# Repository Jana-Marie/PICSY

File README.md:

# PICSY

**UNDER DEVELOPMENT...**

An ESP32 based Pixel-Art-Camera, shooting color-indexed pixel art alike PNGs directly onto an SD card.

<table>
  <tbody>
    <tr>
      <td colspan="2">
        
      </td>
    </tr>
    <tr>
      <td>
        
      </td>
      <td>
        
      </td>
    </tr>
    <tr>
      <td colspan="2">
        
      </td>
    </tr>
    <tr>
      <td colspan="2">
        
      </td>
    </tr>
    <tr>
      <td>
        
      </td>
      <td>
        
      </td>
    </tr>
    <tr>
      <td colspan="2">
        
      </td>
    </tr>
  </tbody>
</table>

### Setup

Flash micropython as per [/main/micropython-bin](https://github.com/Jana-Marie/PICSY/tree/main/micropython-bin), afterwards copy `ubuf2png.py` onto the ESP32-CAM with `ampy -p /dev/ttyUSB0 -b 115200 put ubuf2png.py`

### Usage

This is WIP and will be moved to saving the PNG to a SD card directly soon.

#### Manual usage

Place an SD card into the SD-Card slot and run

```
ampy -p /dev/ttyUSB0 -b 115200 run boot.py
```

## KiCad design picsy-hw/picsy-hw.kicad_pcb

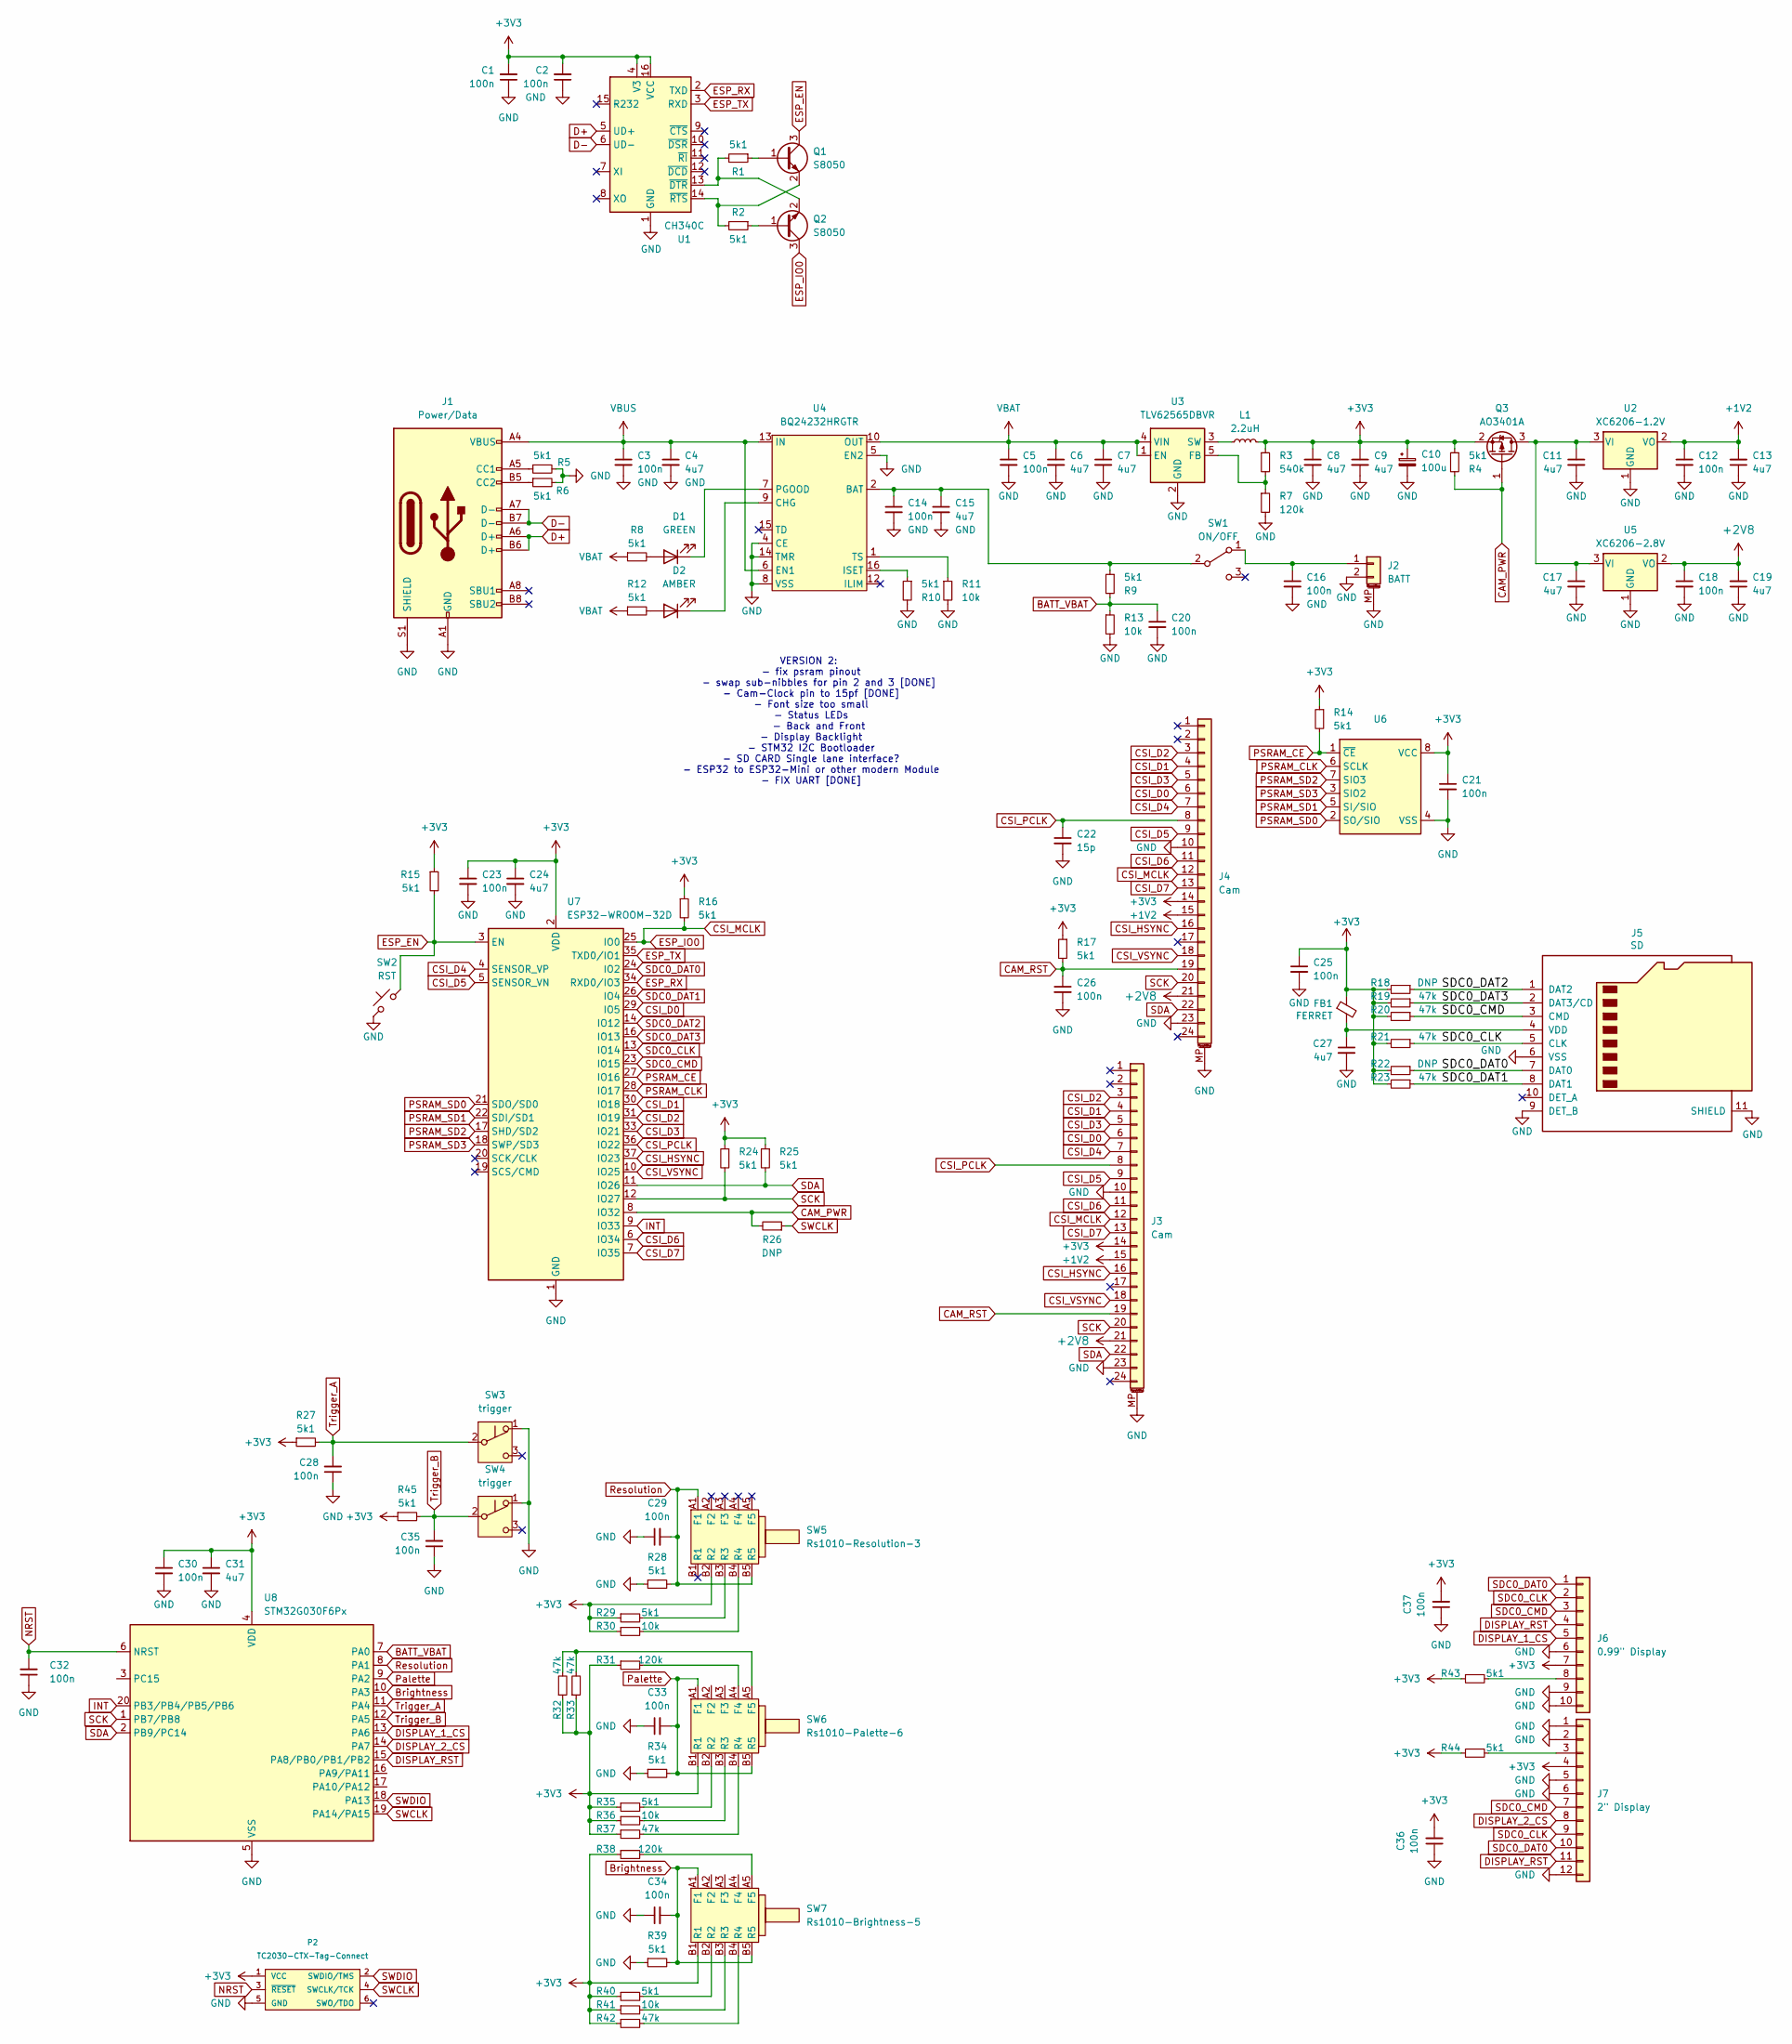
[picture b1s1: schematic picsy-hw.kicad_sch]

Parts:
C1, C2, C3, C5, C12, C14, C16, C18, C20, C21, C23, C25, C26, C28, C29, C30, C32, C33, C34, C35, C36, C37: 100n; C_0402
C4, C6, C7, C8, C9, C11, C13, C15, C17, C19, C24, C27, C31: 4u7; C_0603
C10: 100u; CP_Elec_6.3x5.4
C22: 15p; C_0402
D1: GREEN; LED_0603_1608Metric
D2: AMBER; LED_0603_1608Metric
FB1: FERRET; R_0805
J1: Power/Data; USB-C 16Pin
J2: BATT; Molex_PicoBlade_53261-0271_1x02-1MP_P1.25mm_Horizontal
J3, J4: Cam; TE_2-1734839-4_1x24-1MP_P0.5mm_Horizontal
J5: SD; microSD_HC_Hirose_DM3D-SF
J6: 0.99" Display; 0.99Inch-IPS-GC9D01
J7: 2" Display; 2.0Inch-IPS-ST7789
L1: 2.2uH; L_2512_6332Metric
P2: TC2030-CTX-Tag-Connect; TC2030
Q1, Q2: S8050; SOT-23
Q3: AO3401A; SOT-23
R1, R2, R4, R5, R6, R8, R9, R10, R12, R14, R15, R16, R17, R24, R25, R27, R28, R29, R34, R35, R39, R40, R43, R44, R45: 5k1; R_0402
R3: 540k; R_0402
R7, R31, R38: 120k; R_0402
R11, R13, R30, R36, R41: 10k; R_0402
R18, R22, R26: DNP; R_0402
R19, R20, R21, R23, R32, R33, R37, R42: 47k; R_0402
SW1: ON/OFF; SK-12D07VG4
SW2: RST; SW_SPST_EVQP7C
SW3: trigger; Microswitch_L
SW4: trigger; Microswitch_R
SW5: Rs1010-Resolution-3; Rs1010
SW6: Rs1010-Palette-6; Rs1010
SW7: Rs1010-Brightness-5; Rs1010
U1: CH340C; SOIC-16_3.9x9.9mm_P1.27mm
U2: XC6206-1.2V; SOT-23-3
U3: TLV62565DBVR; SOT-23-5
U4: BQ24232HRGTR; QFN-16-1EP_3x3mm_P0.5mm_EP1.7x1.7mm
U5: XC6206-2.8V; SOT-23-3
U6: SOIC-8_3.9x4.9mm_P1.27mm
U7: ESP32-WROOM-32D; ESP32-WROOM-32U
U8: STM32G030F6Px; TSSOP-20_4.4x6.5mm_P0.65mm

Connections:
+1V2: C12.1, C13.2, J3.15, J4.15, U2.2 (VO)
+2V8: C18.1, C19.2, J3.21, J4.21, U5.2 (VO)
+3V3: C1.2, C2.2, C8.1, C9.1, C10.1, C21.1, C23.1, C24.1, C25.1, C30.1, C31.1, C36.2, C37.2, FB1.1, J3.14, J4.14, J6.7, J7.4, L1.2, P2.1 (VCC), Q3.2 (S), R3.1, R4.1, R14.1, R15.1, R16.1, R17.1, R18.2, R19.2, R20.2, R21.2, R22.2, R23.2, R24.1, R25.1, R27.1, R29.1, R30.1, R31.1, R32.1, R33.1, R35.1, R36.1, R37.1, R38.1, R40.1, R41.1, R42.1, R43.1, R44.1, R45.1, SW5.B2 (R2), SW6.B1 (R1), SW7.B1 (R1), U1.4 (V3), U1.16 (VCC), U6.8 (VCC), U7.2 (VDD), U8.4 (VDD)
BATT_VBAT: C20.1, R9.2, R13.1, U8.7 (PA0)
Brightness: C34.2, R39.2, SW7.A1 (F1), SW7.B5 (R5), U8.10 (PA3)
CAM_PWR: Q3.1 (G), R4.2, R26.2, U7.8 (IO32)
CAM_RST: C26.1, J3.19, J4.19, R17.2
CSI_D0: J3.6, J4.6, U7.29 (IO5)
CSI_D1: J3.4, J4.4, U7.30 (IO18)
CSI_D2: J3.3, J4.3, U7.31 (IO19)
CSI_D3: J3.5, J4.5, U7.33 (IO21)
CSI_D4: J3.7, J4.7, U7.4 (SENSOR_VP)
CSI_D5: J3.9, J4.9, U7.5 (SENSOR_VN)
CSI_D6: J3.11, J4.11, U7.6 (IO34)
CSI_D7: J3.13, J4.13, U7.7 (IO35)
CSI_HSYNC: J3.16, J4.16, U7.37 (IO23)
CSI_MCLK: J3.12, J4.12, Q2.3 (C), R16.2, U7.25 (IO0)
CSI_PCLK: C22.1, J3.8, J4.8, U7.36 (IO22)
CSI_VSYNC: J3.18, J4.18, U7.10 (IO25)
D+: J1.A6 (D+), J1.B6 (D+), U1.5 (UD+)
D-: J1.A7 (D-), J1.B7 (D-), U1.6 (UD-)
DISPLAY_1_CS: J6.5, U8.13 (PA6)
DISPLAY_2_CS: J7.8, U8.14 (PA7)
DISPLAY_RST: J6.4, J7.11, U8.15 (PA8/PB0/PB1/PB2)
ESP_EN: Q1.3 (C), R15.2, SW2.1, U7.3 (EN)
GND: C1.1, C2.1, C3.2, C4.2, C5.2, C6.2, C7.2, C8.2, C9.2, C10.2, C11.2, C12.2, C13.1, C14.2, C15.2, C16.2, C17.2, C18.2, C19.1, C20.2, C21.2, C22.2, C23.2, C24.2, C25.2, C26.2, C27.2, C28.1, C29.1, C30.2, C31.2, C32.1, C33.1, C34.1, C35.1, C36.1, C37.1, J1.A1 (GND), J1.A12 (GND), J1.B1 (GND), J1.B12 (GND), J1.S1 (SHIELD), J2.2, J2.MP (MountPin), J3.10, J3.23, J3.MP (MountPin), J4.10, J4.23, J4.MP (MountPin), J5.6 (VSS), J5.9 (DET_B), J5.11 (SHIELD), J6.6, J6.9, J6.10, J7.1, J7.2, J7.5, J7.6, J7.12, P2.5 (GND), R5.2, R6.2, R7.2, R10.2, R11.2, R13.2, R28.1, R34.1, R39.1, SW2.2, SW3.1 (A), SW4.1 (A), U1.1 (GND), U2.1 (GND), U3.2 (GND), U4.4 (CE), U4.5 (EN2), U4.8 (VSS), U4.14 (TMR), U4.17 (VSS), U5.1 (GND), U6.4 (VSS), U7.1 (GND), U7.15 (GND), U7.38 (GND), U7.39 (GND), U8.5 (VSS)
INT: U7.9 (IO33), U8.20 (PB3/PB4/PB5/PB6)
NRST: C32.2, P2.3 (~RESET), U8.6 (NRST)
unnamed: D1.2 (A), R8.2
unnamed: D1.1 (K), U4.7 (PGOOD)
unnamed: D2.2 (A), R12.2
unnamed: D2.1 (K), U4.9 (CHG)
unnamed: J1.A5 (CC1), R5.1
unnamed: J1.B5 (CC2), R6.1
unnamed: C16.1, J2.1, SW1.1 (A)
unnamed: C27.1, FB1.2, J5.4 (VDD)
unnamed: J6.8, R43.2
unnamed: J7.3, R44.2
unnamed: Q1.1 (B), R1.1
unnamed: Q1.2 (E), R2.2, U1.14 (~RTS)
unnamed: Q2.1 (B), R2.1
unnamed: Q2.2 (E), R1.2, U1.13 (~DTR)
unnamed: C11.1, C17.1, Q3.3 (D), U2.3 (VI), U5.3 (VI)
unnamed: C14.1, C15.1, R9.1, SW1.2 (B), U4.2 (BAT), U4.3 (BAT)
unnamed: R29.2, SW5.B3 (R3)
unnamed: R30.2, SW5.B4 (R4)
unnamed: R31.2, SW6.A4 (F4)
unnamed: R32.2, R33.2, SW6.A5 (F5)
unnamed: R35.2, SW6.B2 (R2)
unnamed: R36.2, SW6.B3 (R3)
unnamed: R37.2, SW6.B4 (R4)
unnamed: R38.2, SW7.A5 (F5)
unnamed: R40.2, SW7.B2 (R2)
unnamed: R41.2, SW7.B3 (R3)
unnamed: R42.2, SW7.B4 (R4)
unnamed: R3.2, R7.1, U3.5 (FB)
unnamed: L1.1, U3.3 (SW)
unnamed: R10.1, U4.16 (ISET)
unnamed: R11.1, U4.1 (TS)
PSRAM_CE: R14.2, U6.1 (~CE), U7.27 (IO16)
PSRAM_CLK: U6.6 (SCLK), U7.28 (IO17)
PSRAM_SD0: U6.2 (SO/SIO), U7.21 (SDO/SD0)
PSRAM_SD1: U6.5 (SI/SIO), U7.22 (SDI/SD1)
Palette: C33.2, R34.2, SW6.A1 (F1), SW6.B5 (R5), U8.9 (PA2)
Resolution: C29.2, R28.2, SW5.A1 (F1), SW5.B5 (R5), U8.8 (PA1)
SCK: J3.20, J4.20, R24.2, U7.12 (IO27), U8.1 (PB7/PB8)
SDA: J3.22, J4.22, R25.2, U7.11 (IO26), U8.2 (PB9/PC14)
SDC0_CLK: J5.5 (CLK), J6.2, J7.9, R21.1, U7.13 (IO14)
SDC0_CMD: J5.3 (CMD), J6.3, J7.7, R20.1, U7.23 (IO15)
SDC0_DAT0: J5.7 (DAT0), J6.1, J7.10, R22.1, U7.24 (IO2)
SDC0_DAT1: J5.8 (DAT1), R23.1, U7.26 (IO4)
SDC0_DAT2: J5.1 (DAT2), R18.1, U7.14 (IO12)
SDC0_DAT3: J5.2 (DAT3/CD), R19.1, U7.16 (IO13)
SWCLK: P2.4 (SWCLK/TCK), R26.1, U8.19 (PA14/PA15)
SWDIO: P2.2 (SWDIO/TMS), U8.18 (PA13)
Trigger_A: C28.2, R27.2, SW3.2 (B), U8.11 (PA4)
Trigger_B: C35.2, R45.2, SW4.2 (B), U8.12 (PA5)
VBAT: C5.1, C6.1, C7.1, R8.1, R12.1, U3.1 (EN), U3.4 (VIN), U4.10 (OUT), U4.11 (OUT)
VBUS: C3.1, C4.1, J1.A4 (VBUS), J1.A9 (VBUS), J1.B4 (VBUS), J1.B9 (VBUS), U4.6 (EN1), U4.13 (IN)

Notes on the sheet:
VERSION 2: - fix psram pinout - swap sub-nibbles for pin 2 and 3 [DONE] - Cam-Clock pin to 15pf [DONE] - Font size too small - Status LEDs - Back and Front - Display Backlight - STM32 I2C Bootloader - SD CARD Single lane interface? - ESP32 to ESP32-Mini or other modern Module - FIX UART [DONE]

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
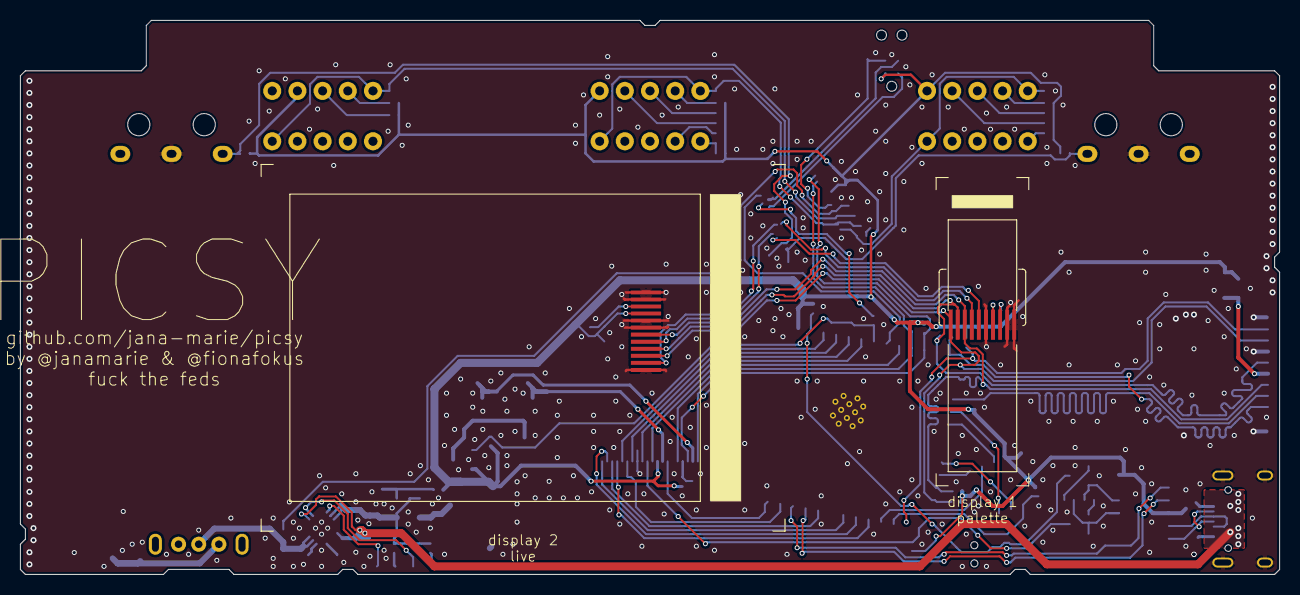
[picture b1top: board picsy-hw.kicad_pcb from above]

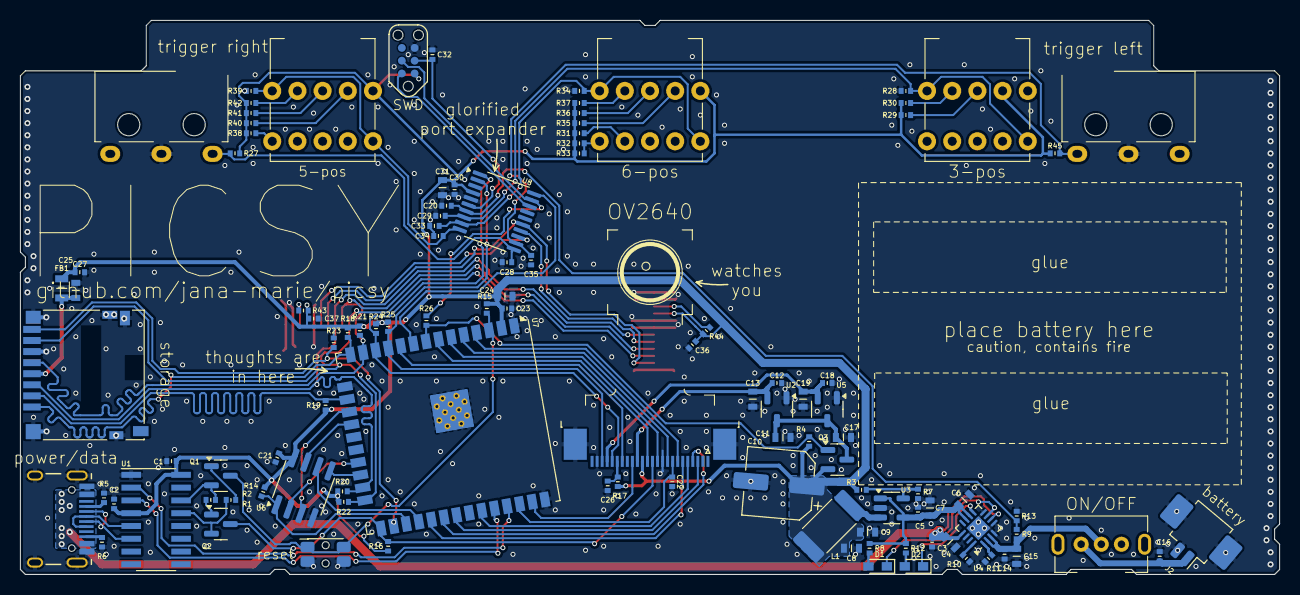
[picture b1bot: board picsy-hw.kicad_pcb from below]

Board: 2 copper layers, 125.0 x 55.0 mm, 111 parts (109 on the bottom side), 83 nets.

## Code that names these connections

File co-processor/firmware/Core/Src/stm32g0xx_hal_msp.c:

/* USER CODE BEGIN Header */
/**
  ******************************************************************************
  * @file         stm32g0xx_hal_msp.c
  * @brief        This file provides code for the MSP Initialization
  *               and de-Initialization codes.
  ******************************************************************************
  * @attention
  *
  * Copyright (c) 2025 STMicroelectronics.
  * All rights reserved.
  *
  * This software is licensed under terms that can be found in the LICENSE file
  * in the root directory of this software component.
  * If no LICENSE file comes with this software, it is provided AS-IS.
  *
  ******************************************************************************
  */
/* USER CODE END Header */

/* Includes ------------------------------------------------------------------*/
#include "main.h"
/* USER CODE BEGIN Includes */

/* USER CODE END Includes */
extern DMA_HandleTypeDef hdma_adc1;

extern DMA_HandleTypeDef hdma_i2c1_rx;

extern DMA_HandleTypeDef hdma_i2c1_tx;

/* Private typedef -----------------------------------------------------------*/
/* USER CODE BEGIN TD */

/* USER CODE END TD */

/* Private define ------------------------------------------------------------*/
/* USER CODE BEGIN Define */

/* USER CODE END Define */

/* Private macro -------------------------------------------------------------*/
/* USER CODE BEGIN Macro */

/* USER CODE END Macro */

/* Private variables ---------------------------------------------------------*/
/* USER CODE BEGIN PV */

/* USER CODE END PV */

/* Private function prototypes -----------------------------------------------*/
/* USER CODE BEGIN PFP */

/* USER CODE END PFP */

/* External functions --------------------------------------------------------*/
/* USER CODE BEGIN ExternalFunctions */

/* USER CODE END ExternalFunctions */

/* USER CODE BEGIN 0 */

/* USER CODE END 0 */
/**
  * Initializes the Global MSP.
  */
void HAL_MspInit(void)
{

  /* USER CODE BEGIN MspInit 0 */

  /* USER CODE END MspInit 0 */

  __HAL_RCC_SYSCFG_CLK_ENABLE();
  __HAL_RCC_PWR_CLK_ENABLE();

  /* System interrupt init*/

  /* USER CODE BEGIN MspInit 1 */

  /* USER CODE END MspInit 1 */
}

/**
* @brief ADC MSP Initialization
* This function configures the hardware resources used in this example
* @param hadc: ADC handle pointer
* @retval None
*/
void HAL_ADC_MspInit(ADC_HandleTypeDef* hadc)
{
  GPIO_InitTypeDef GPIO_InitStruct = {0};
  if(hadc->Instance==ADC1)
  {
  /* USER CODE BEGIN ADC1_MspInit 0 */

  /* USER CODE END ADC1_MspInit 0 */
    /* Peripheral clock enable */
    __HAL_RCC_ADC_CLK_ENABLE();

    __HAL_RCC_GPIOA_CLK_ENABLE();
    /**ADC1 GPIO Configuration
    PA0     ------> ADC1_IN0
    PA1     ------> ADC1_IN1
    PA2     ------> ADC1_IN2
    PA3     ------> ADC1_IN3
    */
    GPIO_InitStruct.Pin = VBAT_Pin|DITHER_Pin|PALETTE_Pin|EXPOSURE_Pin;
    GPIO_InitStruct.Mode = GPIO_MODE_ANALOG;
    GPIO_InitStruct.Pull = GPIO_NOPULL;
    HAL_GPIO_Init(GPIOA, &GPIO_InitStruct);

    /* ADC1 DMA Init */
    /* ADC1 Init */
    hdma_adc1.Instance = DMA1_Channel3;
    hdma_adc1.Init.Request = DMA_REQUEST_ADC1;
    hdma_adc1.Init.Direction = DMA_PERIPH_TO_MEMORY;
    hdma_adc1.Init.PeriphInc = DMA_PINC_DISABLE;
    hdma_adc1.Init.MemInc = DMA_MINC_ENABLE;
    hdma_adc1.Init.PeriphDataAlignment = DMA_PDATAALIGN_HALFWORD;
    hdma_adc1.Init.MemDataAlignment = DMA_MDATAALIGN_HALFWORD;
    hdma_adc1.Init.Mode = DMA_CIRCULAR;
    hdma_adc1.Init.Priority = DMA_PRIORITY_MEDIUM;
    if (HAL_DMA_Init(&hdma_adc1) != HAL_OK)
    {
      Error_Handler();
    }

    __HAL_LINKDMA(hadc,DMA_Handle,hdma_adc1);

  /* USER CODE BEGIN ADC1_MspInit 1 */

  /* USER CODE END ADC1_MspInit 1 */

  }

}

/**
* @brief ADC MSP De-Initialization
* This function freeze the hardware resources used in this example
* @param hadc: ADC handle pointer
* @retval None
*/
void HAL_ADC_MspDeInit(ADC_HandleTypeDef* hadc)
{
  if(hadc->Instance==ADC1)
  {
  /* USER CODE BEGIN ADC1_MspDeInit 0 */

  /* USER CODE END ADC1_MspDeInit 0 */
    /* Peripheral clock disable */
    __HAL_RCC_ADC_CLK_DISABLE();

    /**ADC1 GPIO Configuration
    PA0     ------> ADC1_IN0
    PA1     ------> ADC1_IN1
    PA2     ------> ADC1_IN2
    PA3     ------> ADC1_IN3
    */
    HAL_GPIO_DeInit(GPIOA, VBAT_Pin|DITHER_Pin|PALETTE_Pin|EXPOSURE_Pin);

    /* ADC1 DMA DeInit */
    HAL_DMA_DeInit(hadc->DMA_Handle);
  /* USER CODE BEGIN ADC1_MspDeInit 1 */

  /* USER CODE END ADC1_MspDeInit 1 */
  }

}

/**
* @brief I2C MSP Initialization
* This function configures the hardware resources used in this example
* @param hi2c: I2C handle pointer
* @retval None
*/
void HAL_I2C_MspInit(I2C_HandleTypeDef* hi2c)
{
  GPIO_InitTypeDef GPIO_InitStruct = {0};
  RCC_PeriphCLKInitTypeDef PeriphClkInit = {0};
  if(hi2c->Instance==I2C1)
  {
  /* USER CODE BEGIN I2C1_MspInit 0 */

  /* USER CODE END I2C1_MspInit 0 */

  /** Initializes the peripherals clocks
  */
    PeriphClkInit.PeriphClockSelection = RCC_PERIPHCLK_I2C1;
    PeriphClkInit.I2c1ClockSelection = RCC_I2C1CLKSOURCE_PCLK1;
    if (HAL_RCCEx_PeriphCLKConfig(&PeriphClkInit) != HAL_OK)
    {
      Error_Handler();
    }

    __HAL_RCC_GPIOB_CLK_ENABLE();
    /**I2C1 GPIO Configuration
    PB8     ------> I2C1_SCL
    PB9     ------> I2C1_SDA
    */
    GPIO_InitStruct.Pin = GPIO_PIN_8|GPIO_PIN_9;
    GPIO_InitStruct.Mode = GPIO_MODE_AF_OD;
    GPIO_InitStruct.Pull = GPIO_NOPULL;
    GPIO_InitStruct.Speed = GPIO_SPEED_FREQ_LOW;
    GPIO_InitStruct.Alternate = GPIO_AF6_I2C1;
    HAL_GPIO_Init(GPIOB, &GPIO_InitStruct);

    /* Peripheral clock enable */
    __HAL_RCC_I2C1_CLK_ENABLE();

    /* I2C1 DMA Init */
    /* I2C1_RX Init */
    hdma_i2c1_rx.Instance = DMA1_Channel1;
    hdma_i2c1_rx.Init.Request = DMA_REQUEST_I2C1_RX;
    hdma_i2c1_rx.Init.Direction = DMA_PERIPH_TO_MEMORY;
    hdma_i2c1_rx.Init.PeriphInc = DMA_PINC_DISABLE;
    hdma_i2c1_rx.Init.MemInc = DMA_MINC_ENABLE;
    hdma_i2c1_rx.Init.PeriphDataAlignment = DMA_PDATAALIGN_BYTE;
    hdma_i2c1_rx.Init.MemDataAlignment = DMA_MDATAALIGN_BYTE;
    hdma_i2c1_rx.Init.Mode = DMA_NORMAL;
    hdma_i2c1_rx.Init.Priority = DMA_PRIORITY_LOW;
    if (HAL_DMA_Init(&hdma_i2c1_rx) != HAL_OK)
    {
      Error_Handler();
    }

    __HAL_LINKDMA(hi2c,hdmarx,hdma_i2c1_rx);

    /* I2C1_TX Init */
    hdma_i2c1_tx.Instance = DMA1_Channel2;
    hdma_i2c1_tx.Init.Request = DMA_REQUEST_I2C1_TX;
    hdma_i2c1_tx.Init.Direction = DMA_MEMORY_TO_PERIPH;
    hdma_i2c1_tx.Init.PeriphInc = DMA_PINC_DISABLE;
    hdma_i2c1_tx.Init.MemInc = DMA_MINC_ENABLE;
    hdma_i2c1_tx.Init.PeriphDataAlignment = DMA_PDATAALIGN_BYTE;
    hdma_i2c1_tx.Init.MemDataAlignment = DMA_MDATAALIGN_BYTE;
    hdma_i2c1_tx.Init.Mode = DMA_NORMAL;
    hdma_i2c1_tx.Init.Priority = DMA_PRIORITY_LOW;
    if (HAL_DMA_Init(&hdma_i2c1_tx) != HAL_OK)
    {
      Error_Handler();
    }

    __HAL_LINKDMA(hi2c,hdmatx,hdma_i2c1_tx);

    /* I2C1 interrupt Init */
    HAL_NVIC_SetPriority(I2C1_IRQn, 0, 0);
    HAL_NVIC_EnableIRQ(I2C1_IRQn);
  /* USER CODE BEGIN I2C1_MspInit 1 */

  /* USER CODE END I2C1_MspInit 1 */

  }

}

/**
* @brief I2C MSP De-Initialization
* This function freeze the hardware resources used in this example
* @param hi2c: I2C handle pointer
* @retval None
*/
void HAL_I2C_MspDeInit(I2C_HandleTypeDef* hi2c)
{
  if(hi2c->Instance==I2C1)
  {
  /* USER CODE BEGIN I2C1_MspDeInit 0 */

  /* USER CODE END I2C1_MspDeInit 0 */
    /* Peripheral clock disable */
    __HAL_RCC_I2C1_CLK_DISABLE();

    /**I2C1 GPIO Configuration
    PB8     ------> I2C1_SCL
    PB9     ------> I2C1_SDA
    */
    HAL_GPIO_DeInit(GPIOB, GPIO_PIN_8);

    HAL_GPIO_DeInit(GPIOB, GPIO_PIN_9);

    /* I2C1 DMA DeInit */
    HAL_DMA_DeInit(hi2c->hdmarx);
    HAL_DMA_DeInit(hi2c->hdmatx);

    /* I2C1 interrupt DeInit */
    HAL_NVIC_DisableIRQ(I2C1_IRQn);
  /* USER CODE BEGIN I2C1_MspDeInit 1 */

  /* USER CODE END I2C1_MspDeInit 1 */
  }

}

/**
* @brief TIM_Base MSP Initialization
* This function configures the hardware resources used in this example
* @param htim_base: TIM_Base handle pointer
* @retval None
*/
void HAL_TIM_Base_MspInit(TIM_HandleTypeDef* htim_base)
{
  if(htim_base->Instance==TIM1)
  {
  /* USER CODE BEGIN TIM1_MspInit 0 */

  /* USER CODE END TIM1_MspInit 0 */
    /* Peripheral clock enable */
    __HAL_RCC_TIM1_CLK_ENABLE();
  /* USER CODE BEGIN TIM1_MspInit 1 */

  /* USER CODE END TIM1_MspInit 1 */

  }

}

/**
* @brief TIM_Base MSP De-Initialization
* This function freeze the hardware resources used in this example
* @param htim_base: TIM_Base handle pointer
* @retval None
*/
void HAL_TIM_Base_MspDeInit(TIM_HandleTypeDef* htim_base)
{
  if(htim_base->Instance==TIM1)
  {
  /* USER CODE BEGIN TIM1_MspDeInit 0 */

  /* USER CODE END TIM1_MspDeInit 0 */
    /* Peripheral clock disable */
    __HAL_RCC_TIM1_CLK_DISABLE();
  /* USER CODE BEGIN TIM1_MspDeInit 1 */

  /* USER CODE END TIM1_MspDeInit 1 */
  }

}

/* USER CODE BEGIN 1 */

/* USER CODE END 1 */

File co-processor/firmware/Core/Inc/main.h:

/* USER CODE BEGIN Header */
/**
  ******************************************************************************
  * @file           : main.h
  * @brief          : Header for main.c file.
  *                   This file contains the common defines of the application.
  ******************************************************************************
  * @attention
  *
  * Copyright (c) 2025 STMicroelectronics.
  * All rights reserved.
  *
  * This software is licensed under terms that can be found in the LICENSE file
  * in the root directory of this software component.
  * If no LICENSE file comes with this software, it is provided AS-IS.
  *
  ******************************************************************************
  */
/* USER CODE END Header */

/* Define to prevent recursive inclusion -------------------------------------*/
#ifndef __MAIN_H
#define __MAIN_H

#ifdef __cplusplus
extern "C" {
#endif

/* Includes ------------------------------------------------------------------*/
#include "stm32g0xx_hal.h"

/* Private includes ----------------------------------------------------------*/
/* USER CODE BEGIN Includes */

/* USER CODE END Includes */

/* Exported types ------------------------------------------------------------*/
/* USER CODE BEGIN ET */

/* USER CODE END ET */

/* Exported constants --------------------------------------------------------*/
/* USER CODE BEGIN EC */

/* USER CODE END EC */

/* Exported macro ------------------------------------------------------------*/
/* USER CODE BEGIN EM */

/* USER CODE END EM */

/* Exported functions prototypes ---------------------------------------------*/
void Error_Handler(void);

/* USER CODE BEGIN EFP */

/* USER CODE END EFP */

/* Private defines -----------------------------------------------------------*/
#define VBAT_Pin GPIO_PIN_0
#define VBAT_GPIO_Port GPIOA
#define DITHER_Pin GPIO_PIN_1
#define DITHER_GPIO_Port GPIOA
#define PALETTE_Pin GPIO_PIN_2
#define PALETTE_GPIO_Port GPIOA
#define EXPOSURE_Pin GPIO_PIN_3
#define EXPOSURE_GPIO_Port GPIOA
#define TRIGGER_A_Pin GPIO_PIN_4
#define TRIGGER_A_GPIO_Port GPIOA
#define TRIGGER_A_EXTI_IRQn EXTI4_15_IRQn
#define TRIGGER_B_Pin GPIO_PIN_5
#define TRIGGER_B_GPIO_Port GPIOA
#define TRIGGER_B_EXTI_IRQn EXTI4_15_IRQn
#define DISPLAY_1_CS_Pin GPIO_PIN_6
#define DISPLAY_1_CS_GPIO_Port GPIOA
#define DISPLAY_2_CS_Pin GPIO_PIN_7
#define DISPLAY_2_CS_GPIO_Port GPIOA
#define DISPLAY_RST_Pin GPIO_PIN_0
#define DISPLAY_RST_GPIO_Port GPIOB
#define INT_OUT_Pin GPIO_PIN_3
#define INT_OUT_GPIO_Port GPIOB

/* USER CODE BEGIN Private defines */

/* USER CODE END Private defines */

#ifdef __cplusplus
}
#endif

#endif /* __MAIN_H */

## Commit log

2025-01-13 added firmware
2025-01-13 added code
2025-01-13 added images
2025-01-13 added img
2025-01-13 added desc
2025-01-13 updated boot.py
2025-01-26 Rework file saving
2025-01-26 added camera settings, expanded todo list
2025-02-09 updated hw
2025-02-22 moved binaries
2025-02-22 updated hw files
2025-02-22 added gitignore
2025-02-22 expanded gitignore
2025-02-22 added scad file, case v1
2025-02-22 removed spaces
2025-02-22 updated todo list
2025-02-22 updated schematic
2025-02-22 fixed formatting
2025-02-22 fixed todo formatting
2025-02-22 added IRQ trigger
2025-02-22 added initial STM32 firmware
2025-02-22 appended gitignore
2025-02-22 updated todo-list
2025-02-22 added i2c functionality to FW
2025-02-22 amended todo list
2025-02-22 added todo
2025-02-22 added new frontplate
2025-02-22 added STLs
2025-02-22 updated gitignore
2025-02-22 fixed IRQ bug
2025-02-22 updated schematic todo
2025-02-25 fixed off by one bug
2025-02-25 set default image settings to improve quality
2025-02-25 added external image upscaler
2025-02-25 added type-label
2025-02-25 updated images
2025-02-25 improved image upscaler
